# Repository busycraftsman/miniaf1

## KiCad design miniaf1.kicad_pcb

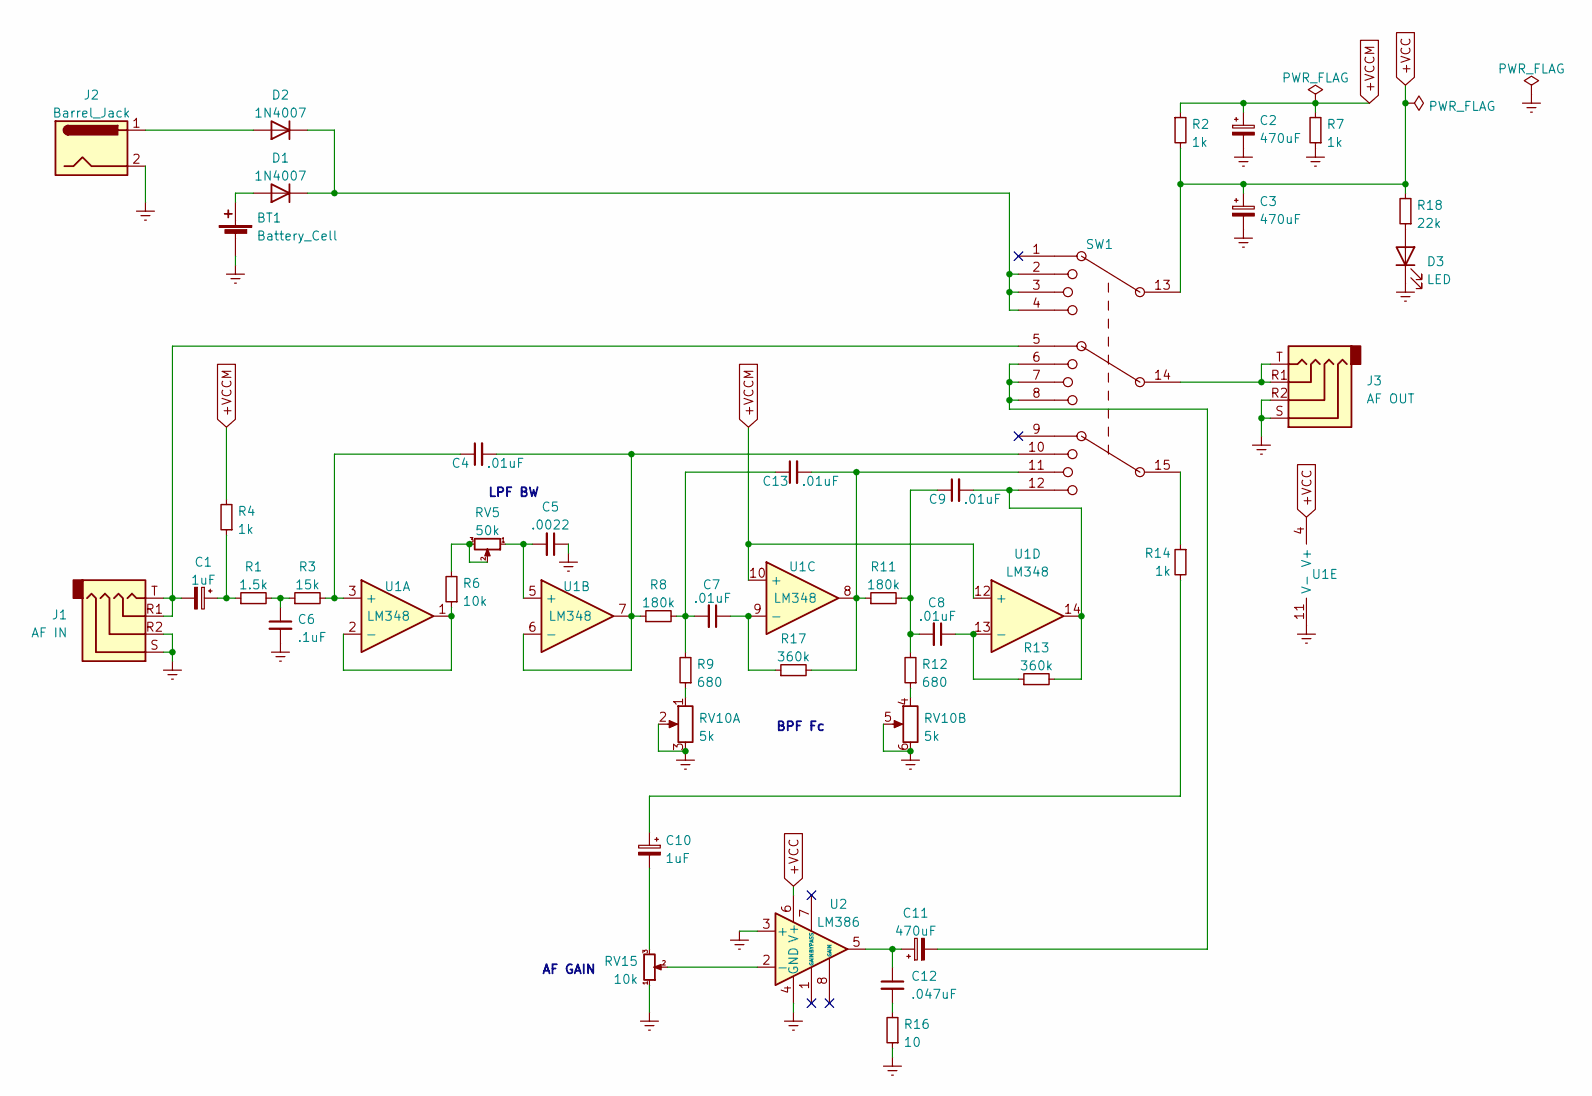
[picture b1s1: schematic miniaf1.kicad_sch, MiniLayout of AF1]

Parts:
BT1: Battery_Cell; PinHeader_1x02_P2.54mm_Vertical
C1, C10: 1uF; CP_Radial_D5.0mm_P2.50mm
C2, C3, C11: 470uF; CP_Radial_D6.3mm_P2.50mm
C4, C7, C8, C9, C13: .01uF; C_0805_2012Metric_Pad1.18x1.45mm_HandSolder
C5: .0022; C_0805_2012Metric_Pad1.18x1.45mm_HandSolder
C6: .1uF; C_0805_2012Metric_Pad1.18x1.45mm_HandSolder
C12: .047uF; C_0805_2012Metric_Pad1.18x1.45mm_HandSolder
D1, D2: 1N4007; D_SOD-123
D3: LED; LED_Rectangular_W3.0mm_H2.0mm
J1: AF IN; Jack_3.5mm_PJ320D_Horizontal
J2: Barrel_Jack; PinHeader_1x02_P2.54mm_Vertical
J3: AF OUT; Jack_3.5mm_PJ320D_Horizontal
R1: 1.5k; R_0805_2012Metric_Pad1.20x1.40mm_HandSolder
R2, R4, R7, R14: 1k; R_0805_2012Metric_Pad1.20x1.40mm_HandSolder
R3: 15k; R_0805_2012Metric_Pad1.20x1.40mm_HandSolder
R6: 10k; R_0805_2012Metric_Pad1.20x1.40mm_HandSolder
R8, R11: 180k; R_0805_2012Metric_Pad1.20x1.40mm_HandSolder
R9, R12: 680; R_0805_2012Metric_Pad1.20x1.40mm_HandSolder
R13, R17: 360k; R_0805_2012Metric_Pad1.20x1.40mm_HandSolder
R16: 10; R_0805_2012Metric_Pad1.20x1.40mm_HandSolder
R18: 22k; R_0805_2012Metric_Pad1.20x1.40mm_HandSolder
RV5: 50k; Potentiometer_wh148_single_3pin
RV10: 5k; Potentiometer_wh148_dual_6pin
RV15: 10k; Potentiometer_wh148_single_3pin
SW1: SW_Rotary3x4; Rotary_switch_RS26_3pole_4throw_widehole_widehole_back_mode
U1: LM348; SOIC-14_3.9x8.7mm_P1.27mm
U2: LM386; SOIC-8_3.9x4.9mm_P1.27mm

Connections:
+VCC: C3.1, R2.2, R18.2, SW1.13, U1.4 (V+), U2.6 (V+)
+VCCM: C2.1, R2.1, R4.2, R7.2, U1.10 (+), U1.12 (+)
GNDREF: BT1.2 (-), C2.2, C3.2, C5.1, C6.2, D3.1 (K), J1.R2, J1.S, J2.2, J3.R2, J3.S, R7.1, R16.1, RV10.2, RV10.3, RV10.5, RV10.6, RV15.1, U1.11 (V-), U2.3 (+), U2.4 (GND)
unnamed: BT1.1 (+), D1.2 (A)
unnamed: C1.1, R1.1, R4.1
unnamed: C1.2, J1.R1, J1.T, SW1.5
unnamed: C4.1, R3.2, U1.3 (+)
unnamed: C4.2, R8.1, SW1.10, U1.6 (-), U1.7
unnamed: C5.2, RV5.1, U1.5 (+)
unnamed: C6.1, R1.2, R3.1
unnamed: C7.1, R17.1, U1.9 (-)
unnamed: C8.1, R13.1, U1.13 (-)
unnamed: C8.2, C9.1, R11.2, R12.2
unnamed: C9.2, R13.2, SW1.12, U1.14
unnamed: C10.1, R14.2
unnamed: C10.2, RV15.3
unnamed: C11.1, C12.1, U2.5
unnamed: C11.2, SW1.6, SW1.7, SW1.8
unnamed: C12.2, R16.2
unnamed: C7.2, C13.1, R8.2, R9.2
unnamed: C13.2, R11.1, R17.2, SW1.11, U1.8
unnamed: D1.1 (K), D2.1 (K), SW1.2, SW1.3, SW1.4
unnamed: D2.2 (A), J2.1
unnamed: D3.2 (A), R18.1
unnamed: J3.R1, J3.T, SW1.14
unnamed: R6.1, U1.1, U1.2 (-)
unnamed: R6.2, RV5.2, RV5.3
unnamed: R9.1, RV10.1
unnamed: R12.1, RV10.4
unnamed: R14.1, SW1.15
unnamed: RV15.2, U2.2 (-)

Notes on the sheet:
AF GAIN
LPF BW
BPF Fc

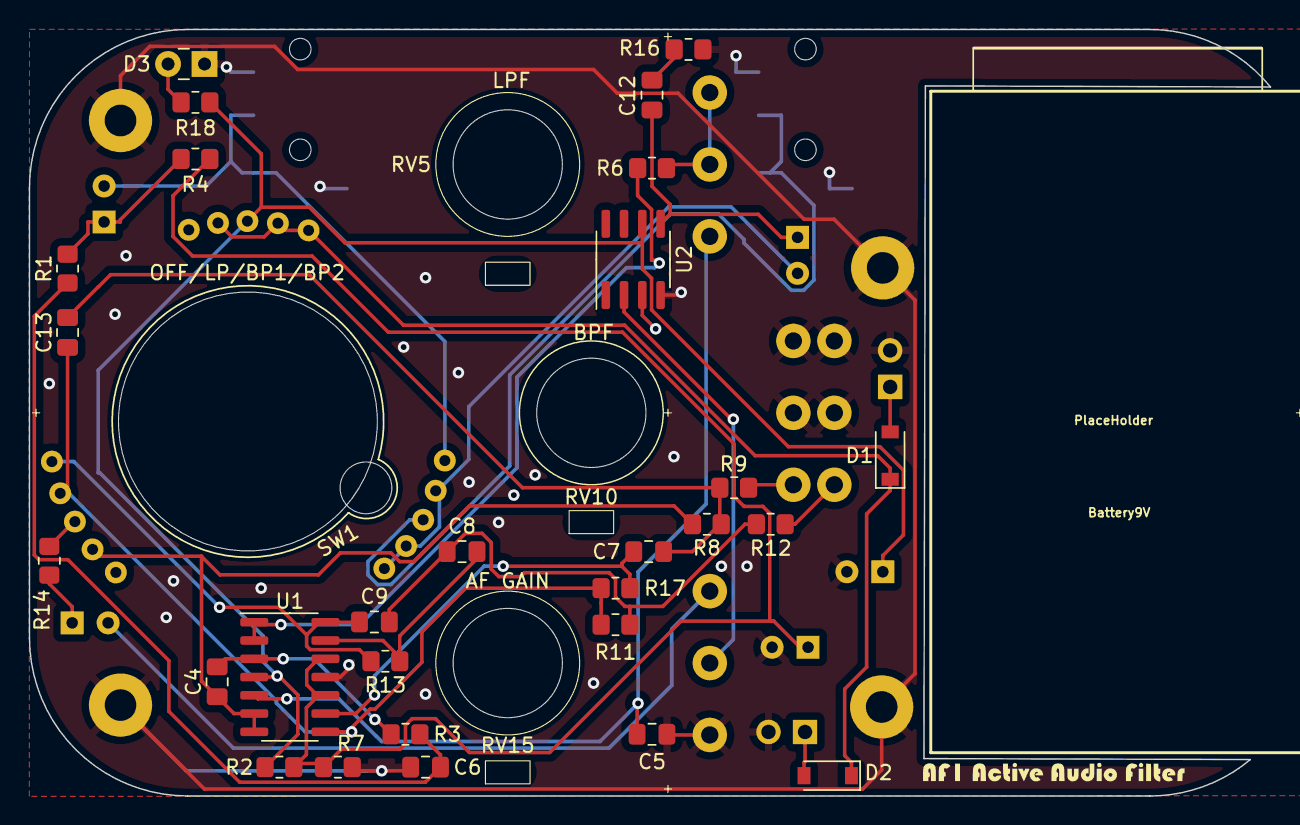
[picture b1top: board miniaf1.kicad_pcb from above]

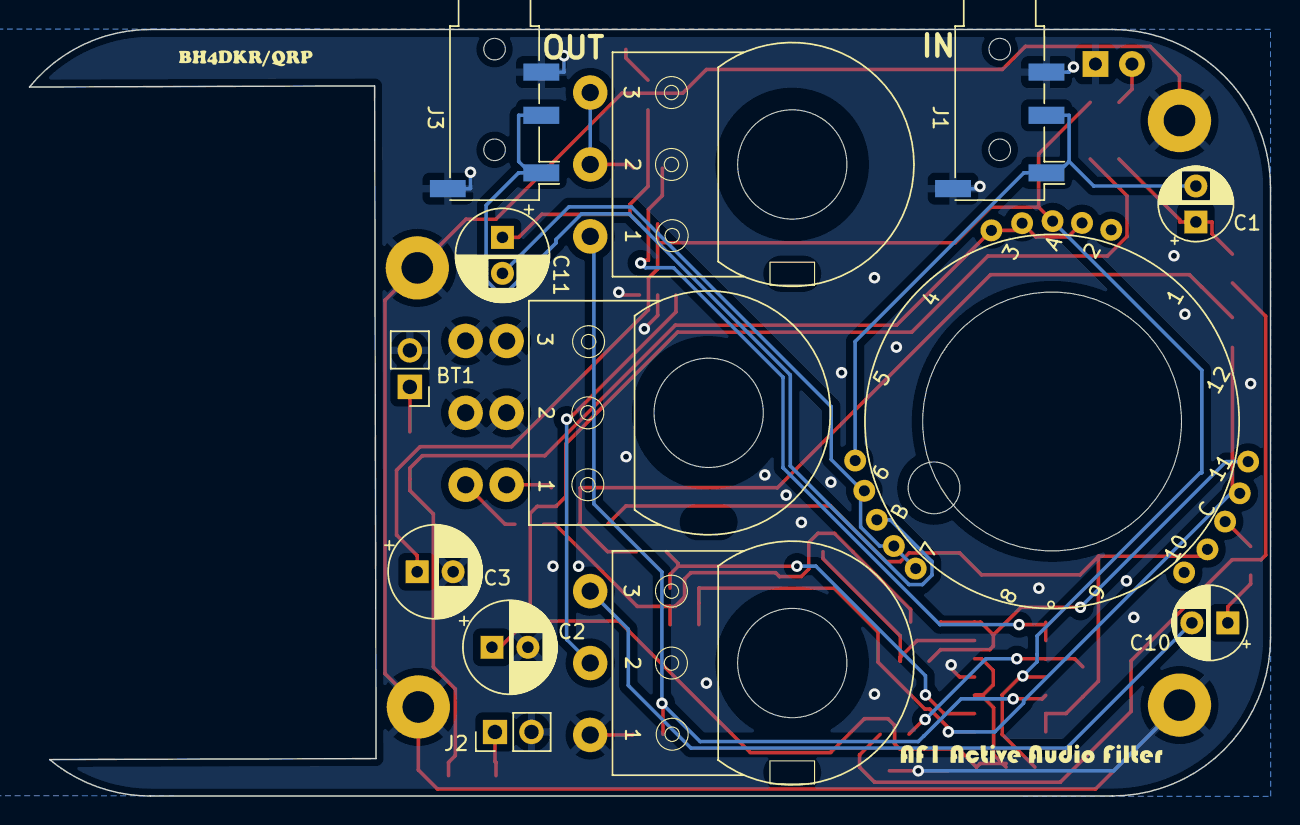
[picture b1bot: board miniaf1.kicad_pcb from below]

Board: 2 copper layers, 86.3 x 53.3 mm, 49 parts (11 on the bottom side), 31 nets.

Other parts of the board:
Battery9V: PlaceHolder; Battery_9V_PlaceHolder_no_pin_for_cut
G001, G002: LOGO; af1 active audio filter
G003: LOGO; bh4dkr_qrp_logo
MOUNT01, MOUNT02, MOUNT03, MOUNT04: MountingHole_2.2mm_M2

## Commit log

2022-06-06 init release version
2022-06-06 refresh WH148 footprint, make more room for easy install
2022-06-07 add enclosure comment in PCB layout for drill
